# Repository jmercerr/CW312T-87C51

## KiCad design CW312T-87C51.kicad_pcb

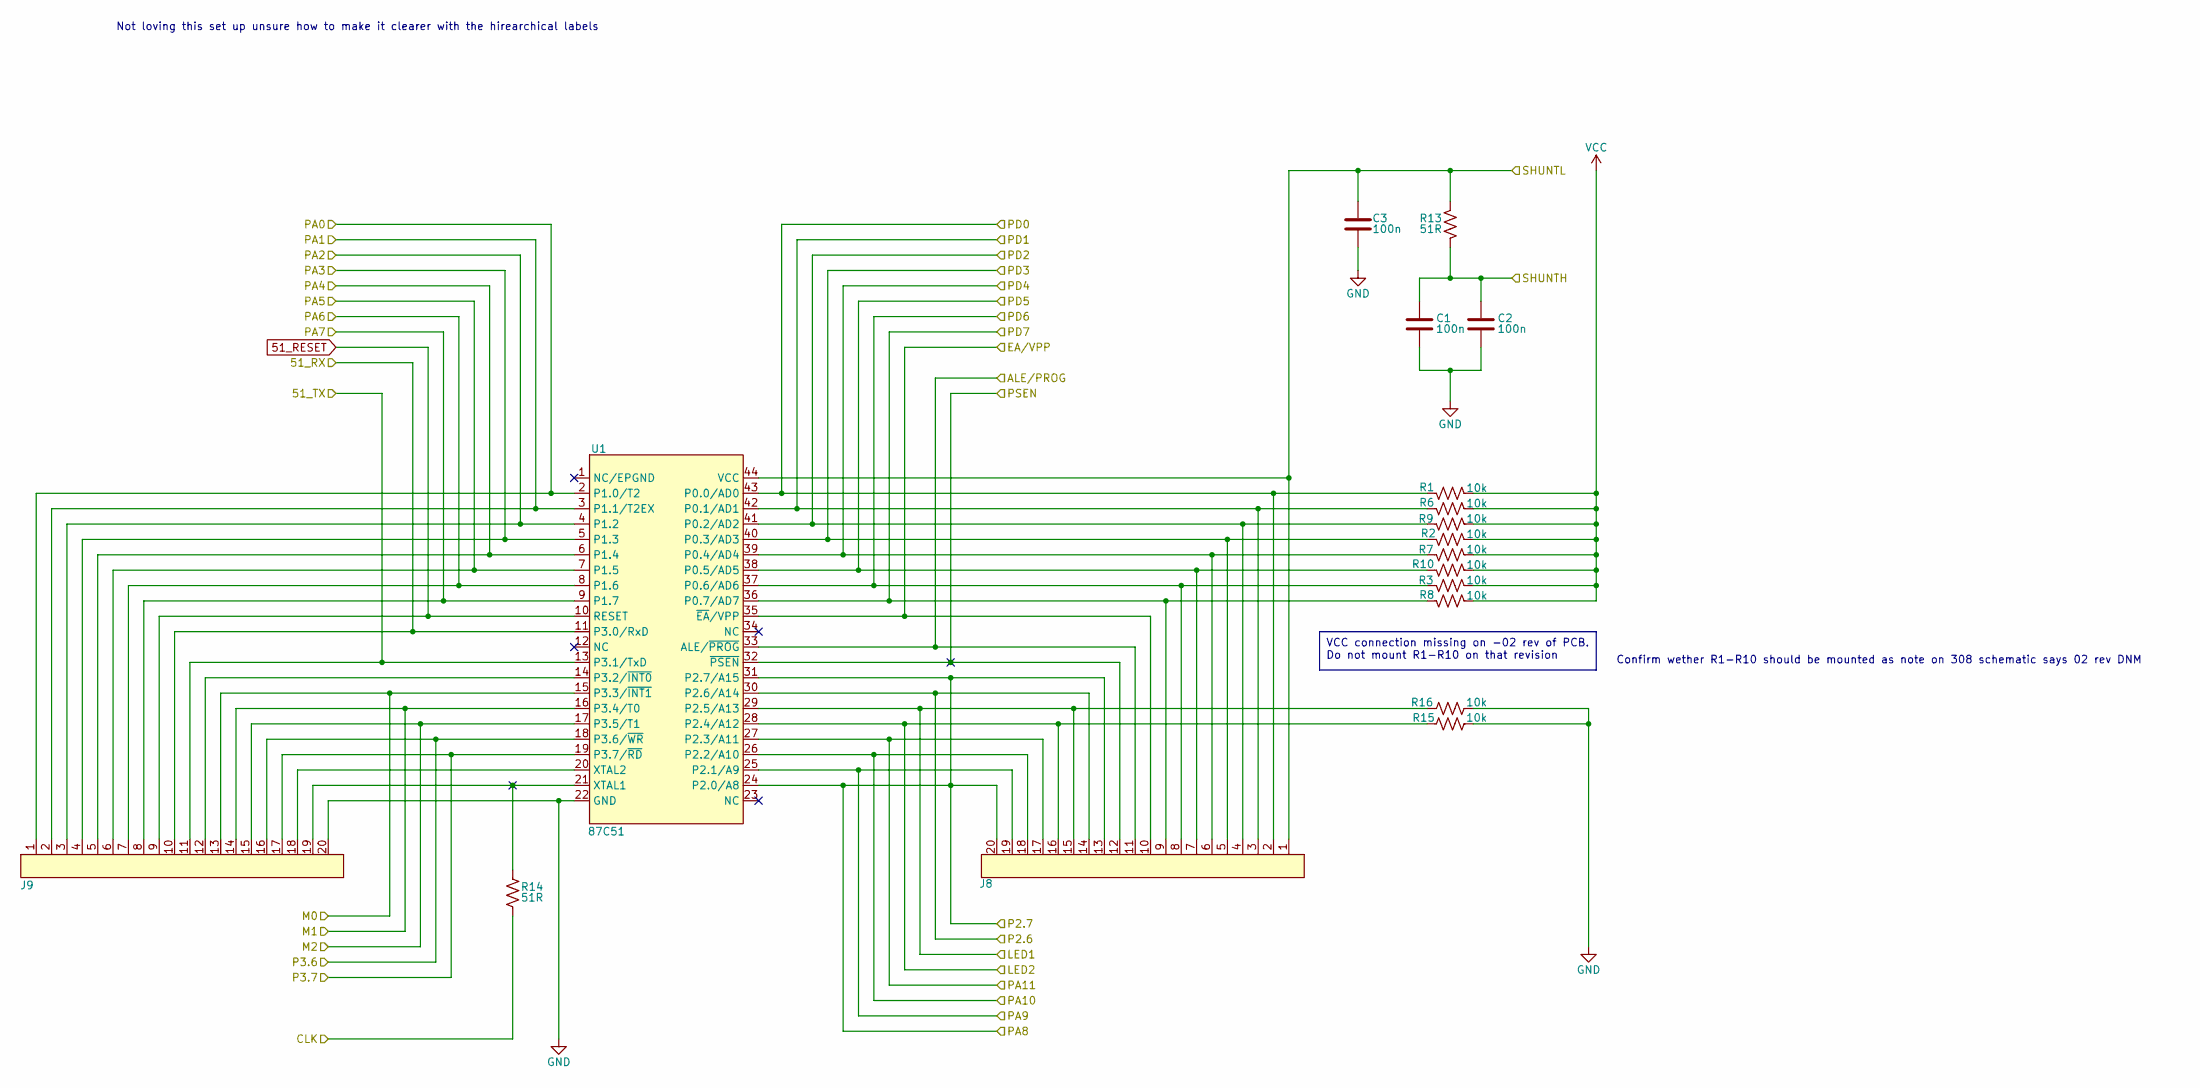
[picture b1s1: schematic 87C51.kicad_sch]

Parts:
C1, C2, C3: CAP_100n_6.3V_0603; C_0603_1608Metric; Manufacturer Part Number CC0603KRX7R5BB104
J8, J9: 68000-220HLF; PinHeader_1x20_P2.54mm_Vertical; Manufacturer Part Number 68000-220HLF
R1, R2, R3, R6, R7, R8, R9, R10, R15, R16: RES_10k_0603; R_0603_1608Metric; Manufacturer Part Number RC0603FR-0710KL
R13, R14: RES_51R_0603; R_0603_1608Metric; Manufacturer Part Number RC0603FR-0751RL
U1: 87C51; PLCC-44_THT-Socket; Manufacturer Part Number 8444-11B1-RK-TP

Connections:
51_RESET: J9.9, U1.10 (RESET); also elsewhere on the board
/87C51/51_RX: J9.10, U1.11 (P3.0/RxD); also elsewhere on the board
/87C51/51_TX: J9.11, U1.13 (P3.1/TxD); also elsewhere on the board
/87C51/ALE/PROG: J8.11, U1.33 (ALE/~PROG); also elsewhere on the board
/87C51/CLK: R14.1; also elsewhere on the board
/87C51/EA/VPP: J8.10, U1.35 (~EA/VPP); also elsewhere on the board
/87C51/LED1: J8.15, R16.2, U1.29 (P2.5/A13); also elsewhere on the board
/87C51/LED2: J8.16, R15.2, U1.28 (P2.4/A12); also elsewhere on the board
/87C51/M0: J9.13, U1.15 (P3.3/~INT1); also elsewhere on the board
/87C51/M1: J9.14, U1.16 (P3.4/T0); also elsewhere on the board
/87C51/M2: J9.15, U1.17 (P3.5/T1); also elsewhere on the board
/87C51/P2.6: J8.14, U1.30 (P2.6/A14); also elsewhere on the board
/87C51/P2.7: J8.13, J8.20, U1.24 (P2.0/A8), U1.31 (P2.7/A15); also elsewhere on the board
/87C51/P3.6: J9.16, U1.18 (P3.6/~WR); also elsewhere on the board
/87C51/P3.7: J9.17, U1.19 (P3.7/~RD); also elsewhere on the board
/87C51/PA1: J9.2, U1.3 (P1.1/T2EX); also elsewhere on the board
/87C51/PA2: J9.3, U1.4 (P1.2); also elsewhere on the board
/87C51/PA3: J9.4, U1.5 (P1.3); also elsewhere on the board
/87C51/PA4: J9.5, U1.6 (P1.4); also elsewhere on the board
/87C51/PA5: J9.6, U1.7 (P1.5); also elsewhere on the board
/87C51/PA6: J9.7, U1.8 (P1.6); also elsewhere on the board
/87C51/PA7: J9.8, U1.9 (P1.7); also elsewhere on the board
/87C51/PA9: J8.19, U1.25 (P2.1/A9); also elsewhere on the board
/87C51/PA10: J8.18, U1.26 (P2.2/A10); also elsewhere on the board
/87C51/PA11: J8.17, U1.27 (P2.3/A11); also elsewhere on the board
/87C51/PD0: J8.2, R1.1, U1.43 (P0.0/AD0); also elsewhere on the board
/87C51/PD1: J8.3, R6.1, U1.42 (P0.1/AD1); also elsewhere on the board
/87C51/PD2: J8.4, R9.1, U1.41 (P0.2/AD2); also elsewhere on the board
/87C51/PD3: J8.5, R2.1, U1.40 (P0.3/AD3); also elsewhere on the board
/87C51/PD4: J8.6, R7.1, U1.39 (P0.4/AD4); also elsewhere on the board
/87C51/PD5: J8.7, R10.1, U1.38 (P0.5/AD5); also elsewhere on the board
/87C51/PD6: J8.8, R3.1, U1.37 (P0.6/AD6); also elsewhere on the board
/87C51/PD7: J8.9, R8.1, U1.36 (P0.7/AD7); also elsewhere on the board
/87C51/PSEN: J8.12, U1.32 (~PSEN); also elsewhere on the board
/87C51/SHUNTL: C3.2, J8.1, R13.2, U1.44 (VCC); also elsewhere on the board
/ATmega325PA-AU/PA0: J9.1, U1.2 (P1.0/T2); also elsewhere on the board
/CW312T_Connections/FILT_HP: C1.2, C2.2, R13.1; also elsewhere on the board
GND: C1.1, C2.1, C3.1, J9.20, R15.1, R16.1, U1.22 (GND); also elsewhere on the board
unnamed: J9.12, U1.14 (P3.2/~INT0)
unnamed: J9.18, U1.20 (XTAL2)
VCC: R1.2, R2.2, R3.2, R6.2, R7.2, R8.2, R9.2, R10.2; also elsewhere on the board

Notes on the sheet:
VCC connection missing on -02 rev of PCB. Do not mount R1-R10 on that revision
Not loving this set up unsure how to make it clearer with the hirearchical labels
Confirm wether R1-R10 should be mounted as note on 308 schematic says 02 rev DNM

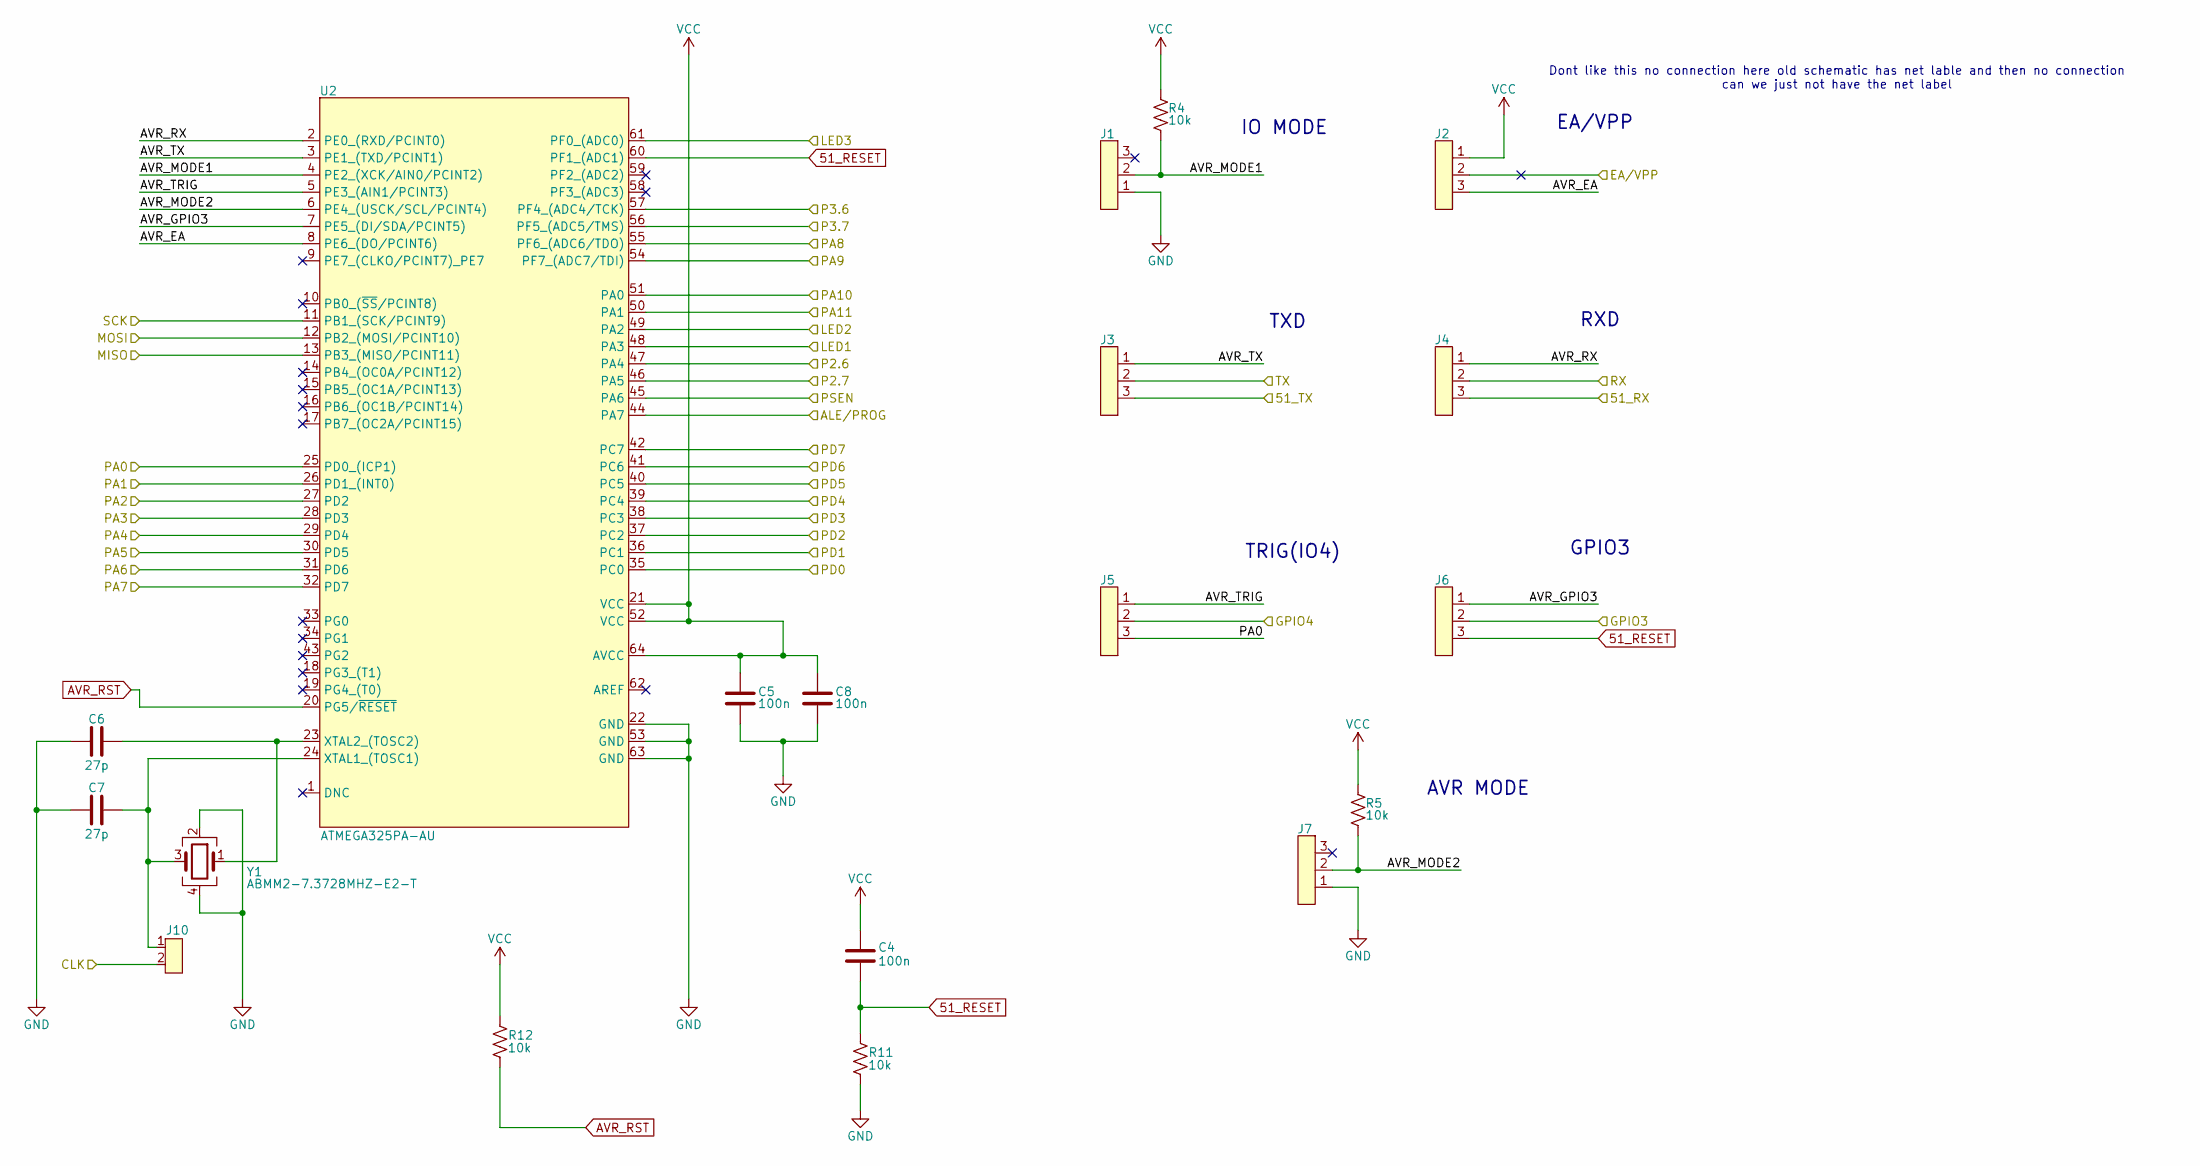
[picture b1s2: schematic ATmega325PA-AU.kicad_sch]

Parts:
C4, C5, C8: CAP_100n_6.3V_0603; C_0603_1608Metric; Manufacturer Part Number CC0603KRX7R5BB104
C6, C7: CAP_27p_50V_0603; C_0603_1608Metric; Manufacturer Part Number C0603C270J5RACTU
J1, J2, J3, J4, J5, J6, J7: 1x3 straight header pins; PinHeader_1x03_P2.54mm_Vertical; Manufacturer Part Number 61300311121
J10: 2Pin_Header_2.54; PinHeader_2x01_P2.54mm_Vertical; Manufacturer Part Number M20-9990246
R4, R5, R11, R12: RES_10k_0603; R_0603_1608Metric; Manufacturer Part Number RC0603FR-0710KL
U2: ATMEGA325PA-AU; TQFP-64_10x10mm_P0.5mm; Manufacturer Part Number ATMEGA325PA-AU
Y1: ABMM2-7.3728MHZ-E2-T; Crystal_SMD_0603-4Pin_6.0x3.5mm; Manufacturer Part Number ABMM2-7.3728MHZ-E2-T

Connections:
51_RESET: C4.1, J6.3, R11.2, U2.60 (PF1_(ADC1)); also elsewhere on the board
/87C51/51_RX: J4.3; also elsewhere on the board
/87C51/51_TX: J3.3; also elsewhere on the board
/87C51/ALE/PROG: U2.44 (PA7); also elsewhere on the board
/87C51/CLK: J10.2; also elsewhere on the board
/87C51/EA/VPP: J2.2; also elsewhere on the board
/87C51/LED1: U2.48 (PA3); also elsewhere on the board
/87C51/LED2: U2.49 (PA2); also elsewhere on the board
/87C51/P2.6: U2.47 (PA4); also elsewhere on the board
/87C51/P2.7: U2.46 (PA5), U2.55 (PF6_(ADC6/TDO)); also elsewhere on the board
/87C51/P3.6: U2.57 (PF4_(ADC4/TCK)); also elsewhere on the board
/87C51/P3.7: U2.56 (PF5_(ADC5/TMS)); also elsewhere on the board
/87C51/PA1: U2.26 (PD1_(INT0)); also elsewhere on the board
/87C51/PA2: U2.27 (PD2); also elsewhere on the board
/87C51/PA3: U2.28 (PD3); also elsewhere on the board
/87C51/PA4: U2.29 (PD4); also elsewhere on the board
/87C51/PA5: U2.30 (PD5); also elsewhere on the board
/87C51/PA6: U2.31 (PD6); also elsewhere on the board
/87C51/PA7: U2.32 (PD7); also elsewhere on the board
/87C51/PA9: U2.54 (PF7_(ADC7/TDI)); also elsewhere on the board
/87C51/PA10: U2.51 (PA0); also elsewhere on the board
/87C51/PA11: U2.50 (PA1); also elsewhere on the board
/87C51/PD0: U2.35 (PC0); also elsewhere on the board
/87C51/PD1: U2.36 (PC1); also elsewhere on the board
/87C51/PD2: U2.37 (PC2); also elsewhere on the board
/87C51/PD3: U2.38 (PC3); also elsewhere on the board
/87C51/PD4: U2.39 (PC4); also elsewhere on the board
/87C51/PD5: U2.40 (PC5); also elsewhere on the board
/87C51/PD6: U2.41 (PC6); also elsewhere on the board
/87C51/PD7: U2.42 (PC7); also elsewhere on the board
/87C51/PSEN: U2.45 (PA6); also elsewhere on the board
/ATmega325PA-AU/AVR_EA: J2.3, U2.8 (PE6_(DO/PCINT6))
/ATmega325PA-AU/AVR_GPIO3: J6.1, U2.7 (PE5_(DI/SDA/PCINT5))
/ATmega325PA-AU/AVR_MODE1: J1.2, R4.1, U2.4 (PE2_(XCK/AIN0/PCINT2))
/ATmega325PA-AU/AVR_MODE2: J7.2, R5.1, U2.6 (PE4_(USCK/SCL/PCINT4))
/ATmega325PA-AU/AVR_RX: J4.1, U2.2 (PE0_(RXD/PCINT0))
/ATmega325PA-AU/AVR_TRIG: J5.1, U2.5 (PE3_(AIN1/PCINT3))
/ATmega325PA-AU/AVR_TX: J3.1, U2.3 (PE1_(TXD/PCINT1))
/ATmega325PA-AU/GPIO3: J6.2; also elsewhere on the board
/ATmega325PA-AU/GPIO4: J5.2; also elsewhere on the board
/ATmega325PA-AU/LED3: U2.61 (PF0_(ADC0)); also elsewhere on the board
/ATmega325PA-AU/MISO: U2.13 (PB3_(MISO/PCINT11)); also elsewhere on the board
/ATmega325PA-AU/MOSI: U2.12 (PB2_(MOSI/PCINT10)); also elsewhere on the board
/ATmega325PA-AU/PA0: J5.3, U2.25 (PD0_(ICP1)); also elsewhere on the board
/ATmega325PA-AU/RX: J4.2; also elsewhere on the board
/ATmega325PA-AU/SCK: U2.11 (PB1_(SCK/PCINT9)); also elsewhere on the board
/ATmega325PA-AU/TX: J3.2; also elsewhere on the board
AVR_RST: R12.1, U2.20 (PG5/~RESET); also elsewhere on the board
GND: C5.1, C6.1, C7.1, C8.1, J1.1, J7.1, R11.1, U2.22 (GND), U2.53 (GND), U2.63 (GND), Y1.2, Y1.4; also elsewhere on the board
unnamed: C7.2, J10.1, U2.24 (XTAL1_(TOSC1)), Y1.3
unnamed: C6.2, U2.23 (XTAL2_(TOSC2)), Y1.1
VCC: C4.2, C5.2, C8.2, J2.1, R4.2, R5.2, R12.2, U2.21 (VCC), U2.52 (VCC), U2.64 (AVCC); also elsewhere on the board

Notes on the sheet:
Dont like this no connection here old schematic has net lable and then no connection can we just not have the net label
TRIG(IO4)
TXD
AVR MODE
EA/VPP
GPIO3
IO MODE
RXD

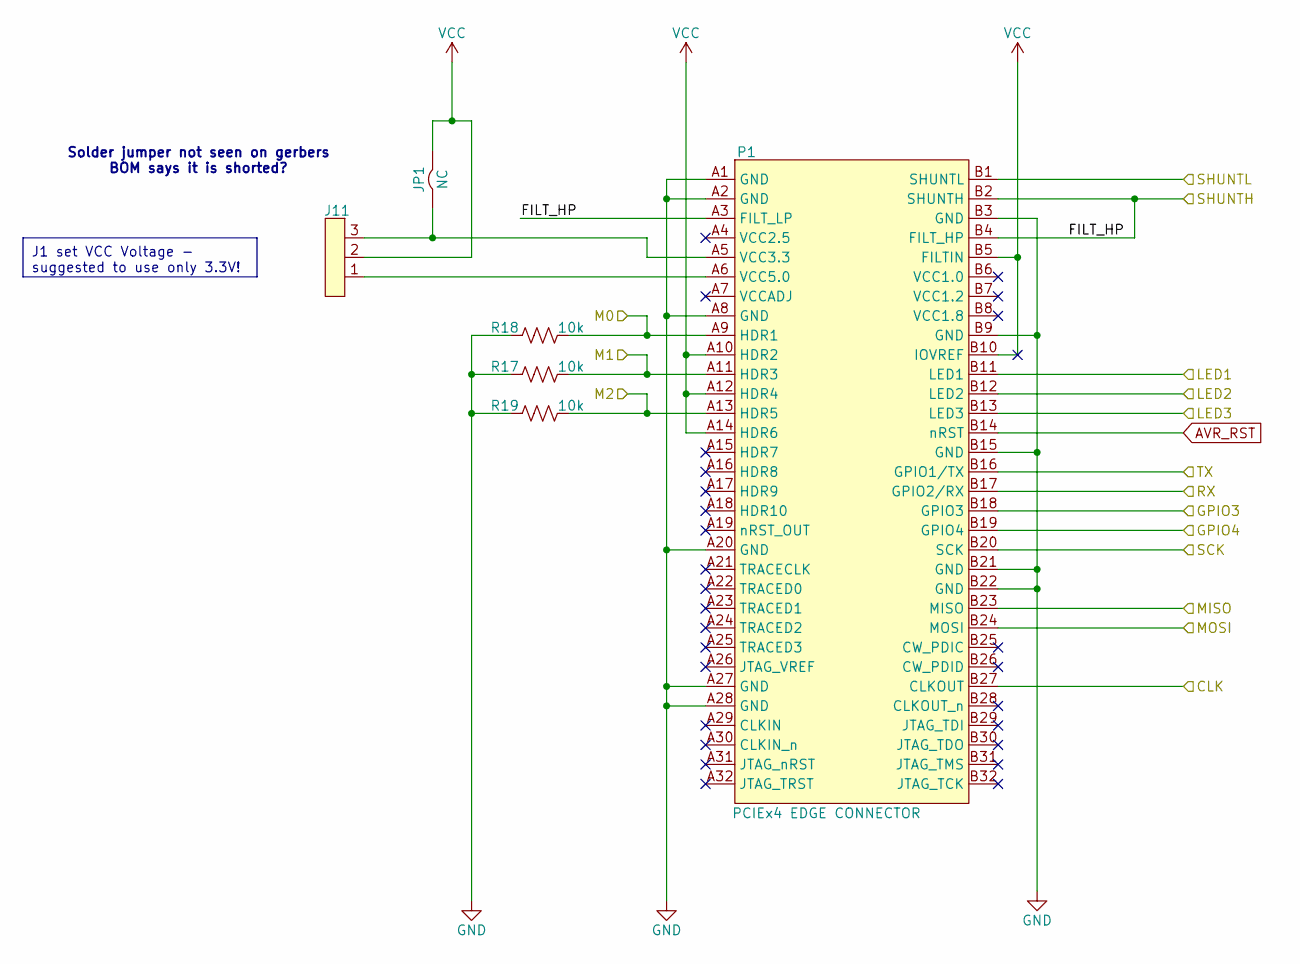
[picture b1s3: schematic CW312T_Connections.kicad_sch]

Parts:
J11: 1x3 straight header pins; PinHeader_1x03_P2.54mm_Vertical; Manufacturer Part Number 61300311121
JP1: SolderJumper-2_P1.3mm_Bridged2Bar_Pad1.0x1.5mm
P1: PCIEx4 EDGE CONNECTOR; CW312_Template
R17, R18, R19: RES_10k_0603; R_0603_1608Metric; Manufacturer Part Number RC0603FR-0710KL

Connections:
/87C51/CLK: P1.B27 (CLKOUT); also elsewhere on the board
/87C51/LED1: P1.B11 (LED1); also elsewhere on the board
/87C51/LED2: P1.B12 (LED2); also elsewhere on the board
/87C51/M0: P1.A9 (HDR1), R18.2; also elsewhere on the board
/87C51/M1: P1.A11 (HDR3), R17.2; also elsewhere on the board
/87C51/M2: P1.A13 (HDR5), R19.2; also elsewhere on the board
/87C51/SHUNTL: P1.B1 (SHUNTL); also elsewhere on the board
/ATmega325PA-AU/GPIO3: P1.B18 (GPIO3); also elsewhere on the board
/ATmega325PA-AU/GPIO4: P1.B19 (GPIO4); also elsewhere on the board
/ATmega325PA-AU/LED3: P1.B13 (LED3); also elsewhere on the board
/ATmega325PA-AU/MISO: P1.B23 (MISO); also elsewhere on the board
/ATmega325PA-AU/MOSI: P1.B24 (MOSI); also elsewhere on the board
/ATmega325PA-AU/RX: P1.B17 (GPIO2/RX); also elsewhere on the board
/ATmega325PA-AU/SCK: P1.B20 (SCK); also elsewhere on the board
/ATmega325PA-AU/TX: P1.B16 (GPIO1/TX); also elsewhere on the board
/CW312T_Connections/FILT_HP: P1.A3 (FILT_LP), P1.B2 (SHUNTH), P1.B4 (FILT_HP); also elsewhere on the board
AVR_RST: P1.B14 (nRST); also elsewhere on the board
GND: P1.A1 (GND), P1.A2 (GND), P1.A8 (GND), P1.A20 (GND), P1.A27 (GND), P1.A28 (GND), P1.B3 (GND), P1.B9 (GND), P1.B15 (GND), P1.B21 (GND), P1.B22 (GND), R17.1, R18.1, R19.1; also elsewhere on the board
unnamed: J11.3, JP1.2, P1.A5 (VCC3.3)
unnamed: J11.1, P1.A6 (VCC5.0)
VCC: J11.2, JP1.1, P1.A10 (HDR2), P1.A12 (HDR4), P1.A14 (HDR6), P1.B5 (FILTIN), P1.B10 (IOVREF); also elsewhere on the board

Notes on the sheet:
J1 set VCC Voltage - suggested to use only 3.3V!
Solder jumper not seen on gerbers BOM says it is shorted?

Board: 2 copper layers, 43 parts (28 on the bottom side), 61 nets, no tracks yet.

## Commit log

2024-12-18 first commit, schematic draft done
2024-12-19 updated schematic after library re-organization
